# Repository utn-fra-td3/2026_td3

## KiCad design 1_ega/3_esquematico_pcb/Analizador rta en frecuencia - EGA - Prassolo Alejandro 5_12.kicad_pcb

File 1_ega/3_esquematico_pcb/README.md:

# esquemático y pcb

Subir en este directorio los archivos de esquemático y PCB en el software que se haya usado y sus vistas en .pdf.

## Esquema de conexiones actual (2026-11-14)

[Esquema modular editable, revision A](project_schematic.svg).
[Vista de impresion A3 horizontal](project_schematic.html).
Abrir la vista de impresion en un navegador y usar Imprimir / Guardar
como PDF. La exportacion automatica con Edge no produjo un archivo
verificable en esta sesion; no se incluye un PDF validado.
Los nombres de red iguales representan conexiones electricas. Los numeros
GPIO no son posiciones fisicas del conector.

Incluye ESP32-WROVER-E, AD9834, UART2, TFT KMRTM28028-SPI, MCP23017,
teclado 4x4 y filtros ADC propuestos. Los colores del cable MCP23017 y
los nombres de pads AD8302 provienen de las fotos recibidas. El dibujo
distingue la arquitectura existente de las conexiones propuestas: no es
un esquema conforme a obra ni un diseno listo para fabricar un PCB.

Siguen pendientes la alimentacion del breakout AD8302, el circuito de
alimentacion/backlight del TFT, el presupuesto de corriente y el frontend
RF. El usuario confirmo mejora del teclado HMI; detector y frontend RF
siguen sin validar. Para el AD8302 no
se debe interpretar la antigua referencia a 5 V de abajo como una
tension de alimentacion confirmada. El esquema deja VCC sin conectar.

## AD8302: frontend provisional (2026-11-07)

Objetivo vigente: DUT de 50 ohm, 100 kHz a 37.5 MHz, ganancia y fase plegada 0..180
grados. La foto del modulo no sustituye un esquema ni confirma ese rango.
No conectar siguiendo solamente el orden de pads de la foto rotada.

### Topologia inicial de prueba

```text
AD9834 Sine1 -> filtro/driver compatible con 50 ohm -> divisor resistivo
																										|          |
																						 DUT entrada     referencia
																										|          |
																						 DUT salida        |
																										|          |
																						 pad opcional  pad opcional
																										|          |
																							 INPA AD8302 INPB AD8302

VM (magnitud) -> aislamiento/filtro/proteccion -> GPIO36 ADC1_CH0
VP (fase)     -> aislamiento/filtro/proteccion -> GPIO34 ADC1_CH6
GND modulo    -> masa comun de senal/ESP32
VREF          -> sin conexion inicial; es una salida, no alimentacion
```

Esta topologia es condicional: INPA/INPB deben presentar las terminaciones
de 50 ohm previstas; si el modulo no las incorpora, redisenar o anadirlas
segun su esquema. INPA actua como carga de la salida del DUT. No anadir
otra carga de 50 ohm en paralelo sin incluirla en el presupuesto de carga.
La rama de referencia aproxima la tension de entrada del DUT solo con
ramas y cargas adaptadas; un DUT desadaptado exige muestreo en su plano
real de entrada o una correccion independiente de esa aproximacion.

Un divisor resistivo de tres puertos puede cubrir frecuencias bajas sin
transformador: tres resistencias nominales de 16.7 ohm en estrella dan
adaptacion de 50 ohm y aproximadamente 6 dB de perdida entre puertos,
cuando todos estan terminados en 50 ohm. Es una opcion de estudio, no un
PCB RF validado. Mantener cables de ramas equivalentes y layout compacto;
a decenas de MHz no usar protoboard ni largos cables Dupont para RF.
Un splitter comercial RF debe especificar funcionamiento a 100 kHz; muchos
no llegan a esa frecuencia. No conectar un tee de dos cargas de 50 ohm:
el generador veria 25 ohm.

La amplitud de 600 mVpp observada con osciloscopio de alta impedancia no
demuestra capacidad de excitar 50 ohm. Determinar impedancia y respuesta
cargada del modulo DDS antes de seleccionar buffer/filtro o atenuadores.
Si esos 600 mVpp fueran realmente sobre 50 ohm, serian unos -0.46 dBm.
El detector tiene rango operativo nominal de -60 a 0 dBm por entrada y
aproximadamente +/-30 dB de relacion. Mantener margen en ambos niveles y
en la relacion; comprobarlos con instrumentacion independiente.

### Conexion ADC y alimentacion

La asignacion GPIO34 es provisional; comprobar acceso fisico y ausencia
de otros usos. Dejar camara desconectada/deshabilitada: GPIO25/26 siguen
reservados para UART2. GPIO16/17 no estan disponibles por la PSRAM WROVER.

Como punto de partida de banco, estudiar resistencia serie de 1 kohm y
100 nF a masa junto a cada ADC: constante de tiempo de 100 us y corte de
aproximadamente 1.59 kHz. No son valores finales: verificar capacidad de
drive y estabilidad del modulo, carga del ADC y asentamiento combinado
con sus filtros. Anadir buffer/proteccion de baja fuga si lo exige el
presupuesto de error o la impedancia. No conectar RF bipolar a estos GPIO.

La marca de suministro parece indicar 5 V, pero verificar tension, polaridad,
regulador y desacoplo con vendedor/esquema antes de energizar. No alimentar
el modulo desde VREF ni desde VCC del adaptador UART. Las salidas del chip
son nominalmente de aproximadamente 0..1.8 V; comprobar las del modulo
antes de conectarlas al ESP32. No aplicar 5 V a GPIO del ESP32.

### Comprobaciones antes de cerrar esquema/BOM

- Obtener esquema o fotos nitidas de ambos lados y confirmar orden/funcion
	de pads, conexiones MSET/PSET y suministro del modulo.
- Verificar terminacion RF, capacitores de entrada, compensacion a baja
	frecuencia y filtros de salidas. Determinan si 100 kHz es alcanzable.
- Definir carga de fuente, divisor, DUT y detector, perdidas/atenuacion y
	amplitud cargada de ambas ramas en toda la banda.
- Revisar pureza del DDS y filtro cerca de 37.5 MHz; Nyquist no garantiza
	una senoide util para medicion.
- Seleccionar conectores/coax de 50 ohm, resistencias del divisor y pads
	solo despues de resolver impedancias. No hay BOM definitiva todavia.

### Secuencia de puesta en marcha

1. Cablear sin alimentacion; revisar masas, polaridad y cortocircuitos.
2. Verificar ADC con DC segura y DMM, sin modulo RF conectado.
3. Energizar modulo con fuente limitada en corriente y tension verificada;
	 comprobar VM/VP/VREF antes de conectarlos a los ADC.
4. Aplicar dos senales del mismo generador con carga y atenuacion conocidas;
	 empezar con margen, por ejemplo alrededor de -20 dBm en cada entrada.
5. Verificar thru y ganancia con atenuadores conocidos en ambas ramas;
	 comprobar signo, pendiente, offset y variacion con frecuencia.
6. Caracterizar fase con referencias verificadas, preferentemente puntos
	 interiores como 45/135 grados. Los extremos 0/180 son menos fiables.
7. Medir un DUT conocido y documentar error y rango realmente validado.

VM/VP no permiten verificar de forma fiable niveles absolutos ni ausencia
de senal. La fase plegada no distingue adelanto/atraso y una resta del thru
no recupera esa informacion. No se trata de un VNA completo ni mide S11.

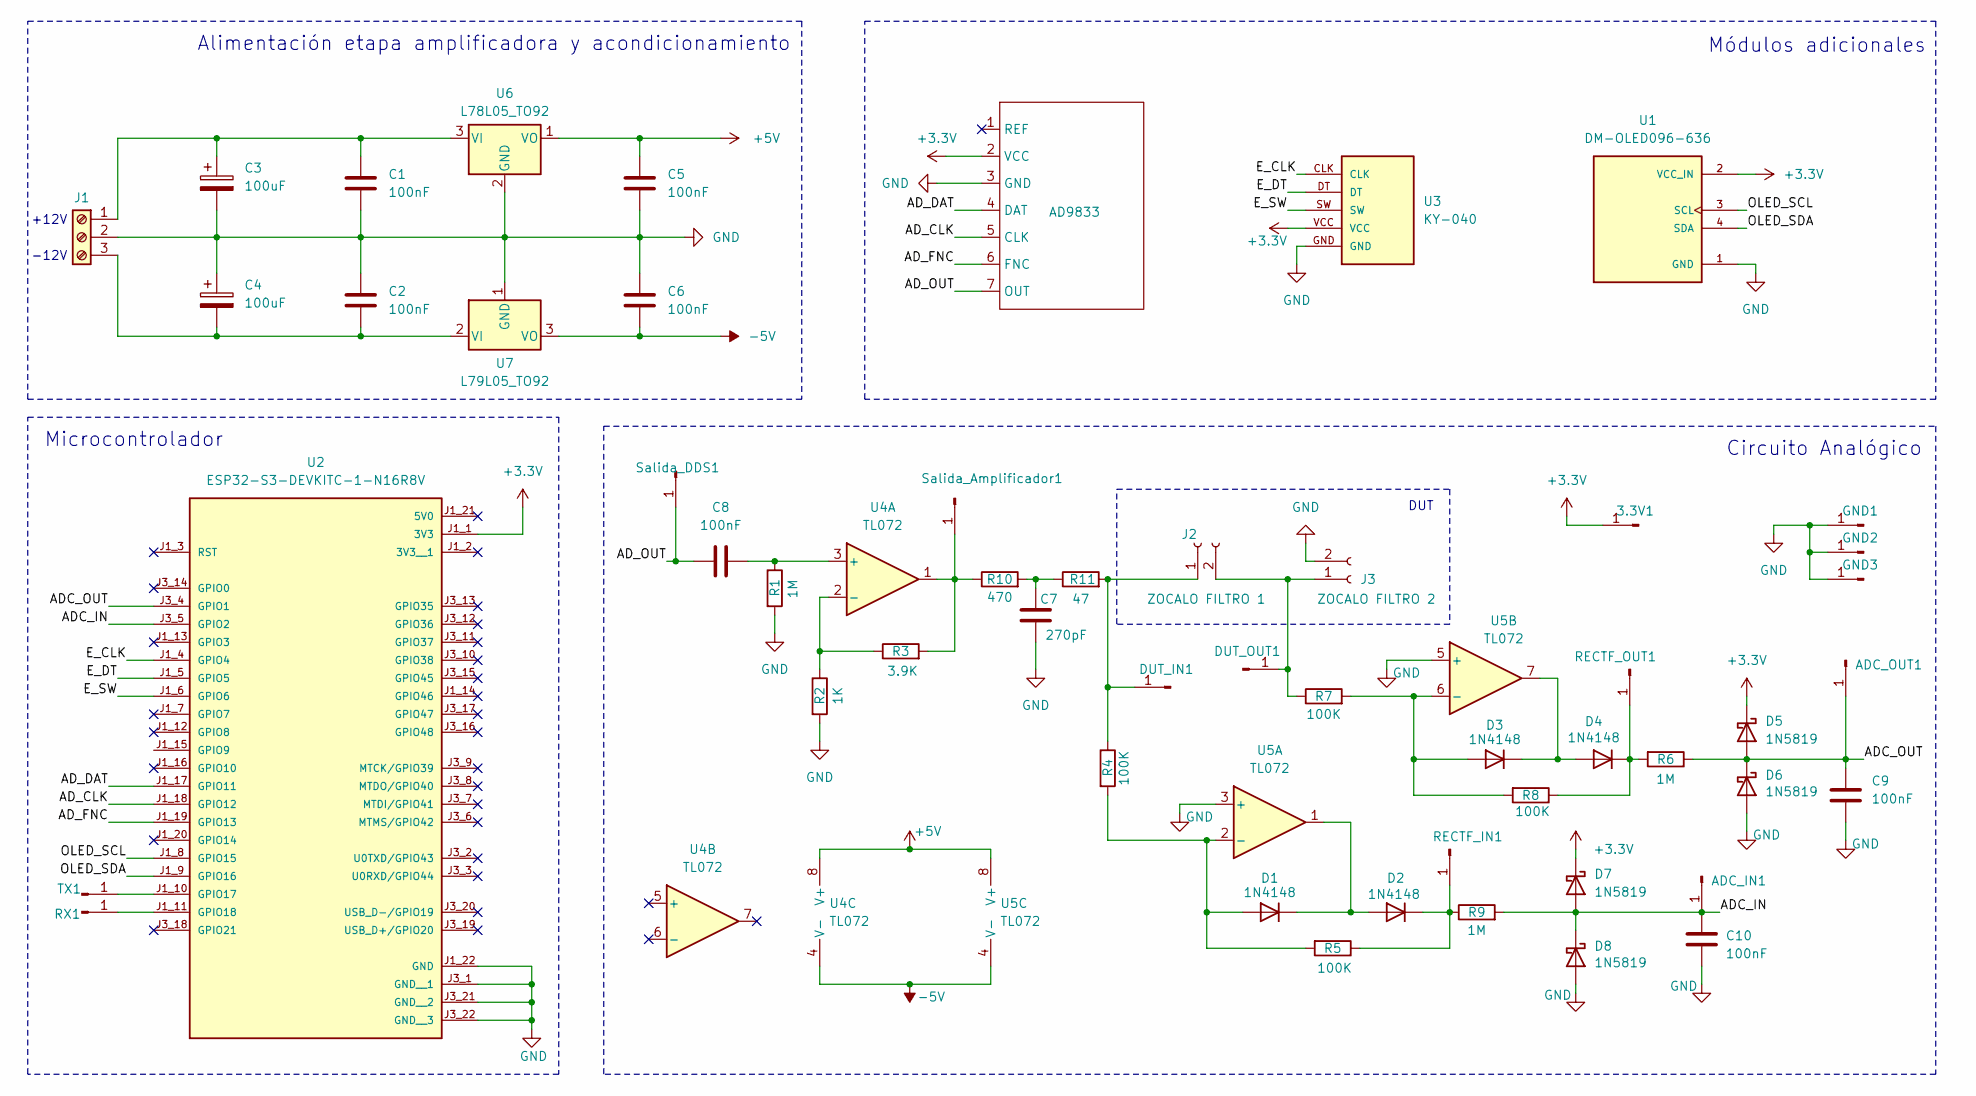
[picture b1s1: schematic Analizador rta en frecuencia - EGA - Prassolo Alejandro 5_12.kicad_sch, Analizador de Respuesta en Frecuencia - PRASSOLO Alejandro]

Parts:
3.3V1: Conn_01x01_Pin; PinHeader_1x01_P2.54mm_Vertical
AD9833: AD9833_MODULO
ADC_IN1: Conn_01x01_Pin; PinHeader_1x01_P2.54mm_Vertical
ADC_OUT1: Conn_01x01_Pin; PinHeader_1x01_P2.54mm_Vertical
C1, C2, C5, C6, C8, C9, C10: 100nF; C_Disc_D5.0mm_W2.5mm_P2.50mm
C3, C4: 100uF; CP_Radial_D6.3mm_P2.50mm
C7: 270pF; C_Disc_D5.0mm_W2.5mm_P2.50mm
D1, D2, D3, D4: 1N4148; D_DO-35_SOD27_P7.62mm_Horizontal
D5, D6, D7, D8: 1N5819; D_DO-41_SOD81_P10.16mm_Horizontal
DUT_IN1: Conn_01x01_Pin; PinHeader_1x01_P2.54mm_Vertical
DUT_OUT1: Conn_01x01_Pin; PinHeader_1x01_P2.54mm_Vertical
GND1, GND2, GND3: Conn_01x01_Pin; PinHeader_1x01_P2.54mm_Vertical
J1: Screw_Terminal_01x03; TerminalBlock_Phoenix_MKDS-1,5-3-5.08_1x03_P5.08mm_Horizont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
J2: ZOCALO FILTRO 1; PinSocket_1x02_P2.54mm_Vertical
J3: ZOCALO FILTRO 2; PinSocket_1x02_P2.54mm_Vertical
R1, R6, R9: 1M; R_Axial_DIN0207_L6.3mm_D2.5mm_P7.62mm_Horizontal
R2: 1K; R_Axial_DIN0207_L6.3mm_D2.5mm_P7.62mm_Horizontal
R3: 3.9K; R_Axial_DIN0207_L6.3mm_D2.5mm_P7.62mm_Horizontal
R4, R5, R7, R8: 100K; R_Axial_DIN0207_L6.3mm_D2.5mm_P7.62mm_Horizontal
R10: 470; R_Axial_DIN0207_L6.3mm_D2.5mm_P7.62mm_Horizontal
R11: 47; R_Axial_DIN0207_L6.3mm_D2.5mm_P7.62mm_Horizontal
RECTF_IN1: Conn_01x01_Pin; PinHeader_1x01_P2.54mm_Vertical
RECTF_OUT1: Conn_01x01_Pin; PinHeader_1x01_P2.54mm_Vertical
RX1: Conn_01x01_Pin; PinHeader_1x01_P2.54mm_Vertical
Salida_Amplificador1: Conn_01x01_Pin; PinHeader_1x01_P2.54mm_Vertical
Salida_DDS1: Conn_01x01_Pin; PinHeader_1x01_P2.54mm_Vertical
TX1: Conn_01x01_Pin; PinHeader_1x01_P2.54mm_Vertical
U1: DM-OLED096-636; MODULE_DM-OLED096-636; PARTREV 2018-09-10
U2: ESP32-S3-DEVKITC-1-N16R8V; XCVR_ESP32-S3-DEVKITC-1-N16R8V; PARTREV 1.1
U3: KY-040; KY-040-PORT
U4, U5: TL072; DIP-8_W7.62mm_Socket
U6: L78L05_TO92; TO-92_Inline
U7: L79L05_TO92; TO-92_Inline

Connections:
+3.3V: 3.3V1.1 (Pin_1_1), AD9833.2 (VCC), D5.1 (K), D7.1 (K), U1.2 (VCC_IN), U2.J1_1 (3V3), U3.VCC
+5V: C5.1, U4.8 (V+), U5.8 (V+), U6.1 (VO)
-5V: C6.2, U4.4 (V-), U5.4 (V-), U7.3 (VO)
/ADC_IN: ADC_IN1.1 (Pin_1_1), C10.1, D7.2 (A), D8.1 (K), R9.2, U2.J3_5 (GPIO2)
/ADC_OUT: ADC_OUT1.1 (Pin_1_1), C9.1, D5.2 (A), D6.1 (K), R6.1, U2.J3_4 (GPIO1)
/AD_CLK: AD9833.5 (CLK), U2.J1_18 (GPIO12)
/AD_DAT: AD9833.4 (DAT), U2.J1_17 (GPIO11)
/AD_FNC: AD9833.6 (FNC), U2.J1_19 (GPIO13)
/AD_OUT: AD9833.7 (OUT), C8.1, Salida_DDS1.1 (Pin_1_1)
/E_CLK: U2.J1_4 (GPIO4), U3.CLK
/E_DT: U2.J1_5 (GPIO5), U3.DT
/E_SW: U2.J1_6 (GPIO6), U3.SW
/OLED_SCL: U1.3 (SCL), U2.J1_8 (GPIO15)
/OLED_SDA: U1.4 (SDA), U2.J1_9 (GPIO16)
GND: AD9833.3 (GND), C1.2, C2.1, C3.2, C4.1, C5.2, C6.1, C7.2, C9.2, C10.2, D6.2 (A), D8.2 (A), GND1.1 (Pin_1_1), GND2.1 (Pin_1_1), GND3.1 (Pin_1_1), J1.2, J3.2, R1.2, R2.2, U1.1 (GND), U2.J1_22 (GND), U2.J3_1 (GND__1), U2.J3_21 (GND__2), U2.J3_22 (GND__3), U3.GND, U5.3 (+), U5.5 (+), U6.2 (GND), U7.1 (GND)
unnamed: C7.1, R10.2, R11.1
unnamed: D1.2 (A), R4.2, R5.2, U5.2 (-)
unnamed: D1.1 (K), D2.2 (A), U5.1
unnamed: D2.1 (K), R5.1, R9.1, RECTF_IN1.1 (Pin_1_1)
unnamed: D3.2 (A), R7.2, R8.2, U5.6 (-)
unnamed: D3.1 (K), D4.2 (A), U5.7
unnamed: D4.1 (K), R6.2, R8.1, RECTF_OUT1.1 (Pin_1_1)
unnamed: DUT_IN1.1 (Pin_1_1), J2.1, R4.1, R11.2
unnamed: DUT_OUT1.1 (Pin_1_1), J2.2, J3.1, R7.1
unnamed: C1.1, C3.1, J1.1, U6.3 (VI)
unnamed: C2.2, C4.2, J1.3, U7.2 (VI)
unnamed: RX1.1 (Pin_1_1), U2.J1_11 (GPIO18)
unnamed: R3.2, R10.1, Salida_Amplificador1.1 (Pin_1_1), U4.1
unnamed: TX1.1 (Pin_1_1), U2.J1_10 (GPIO17)
unnamed: C8.2, R1.1, U4.3 (+)
unnamed: R2.1, R3.1, U4.2 (-)

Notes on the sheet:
Circuito Analógico
DUT
Microcontrolador
Alimentación etapa amplificadora y acondicionamiento
-12V
+12V
Módulos adicionales

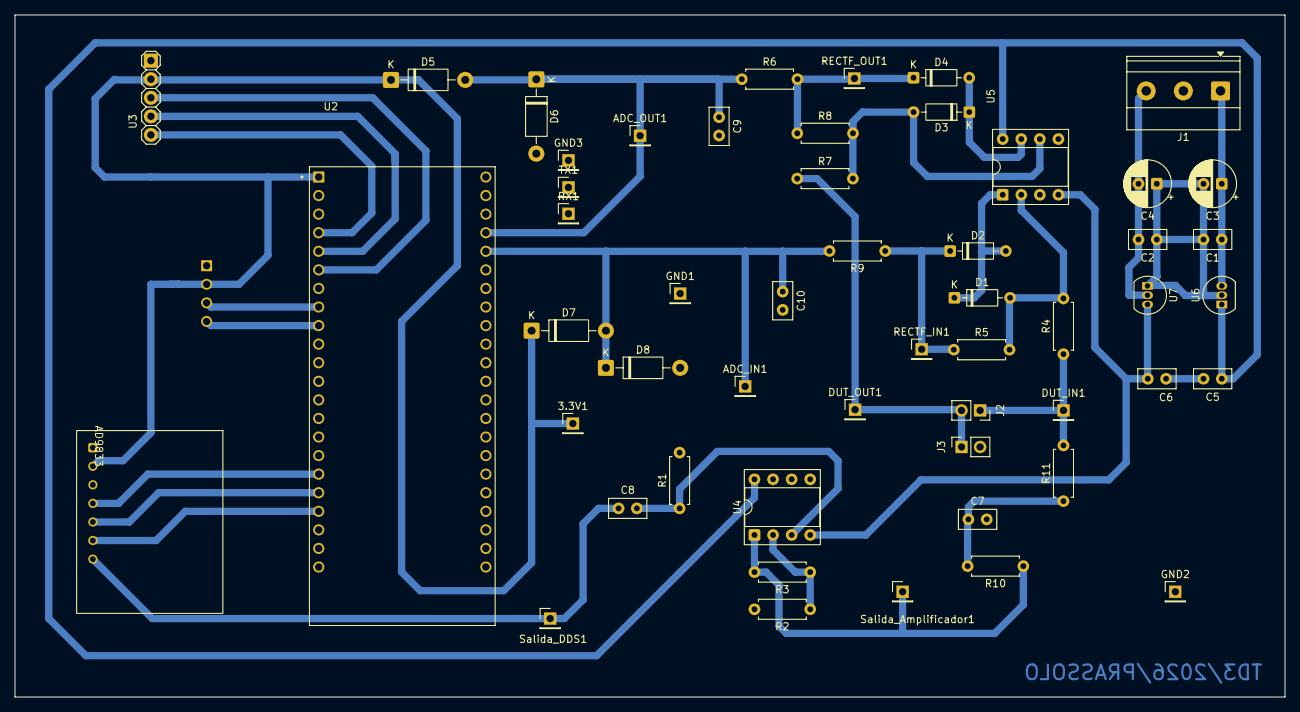
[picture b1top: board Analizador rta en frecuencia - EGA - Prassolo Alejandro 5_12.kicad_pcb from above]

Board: 2 copper layers, 173.7 x 93.3 mm, 54 parts (0 on the bottom side), 31 nets.

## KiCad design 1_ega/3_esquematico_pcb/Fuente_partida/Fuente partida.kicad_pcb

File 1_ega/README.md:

# Proyecto

## EGA: analizador de respuesta en frecuencia

ESP32-WROVER-E, DDS AD9834 y detector AD8302 para ganancia y fase plegada.
Rango admitido por software: **100 kHz a 37.5 MHz**, inclusive, con MCLK
configurado en 75 MHz. No equivale a una banda de medicion RF calibrada.

- [Firmware, GUI/CLI y pruebas](2_workspace/firmware/README.md).
- [Comandos PowerShell de compilacion y carga](2_workspace/firmware/Terminal_command_cheatcode.yaml),
  con Python ESP-IDF explicito y bloques separados `hmi_build`/`hmi_flash`.
- [Esquema y frontend provisional](3_esquematico_pcb/README.md).
- [Diagramas de tareas y bloques](5_referencias/README.md).

La HMI local permite configurar un barrido SINE y ver ganancia/fase en vivo;
A cancela el barrido local y vuelve al inicio. TFT y teclado estan conectados;
el usuario confirmo mejora del teclado con escaneo independiente. AD8302
permanece desconectado: usar SIM hasta validar el frontend.

## Templates para informe IEEE

* [LaTeX en Overleaf](https://www.overleaf.com/latex/templates/ieee-conference-template/grfzhhncsfqn)
* [Google Docs](https://docs.google.com/document/d/1DDDHbyujVE0Jso3ITDVRpF-n_ydSYhf2IecZ8xTA-0w/preview?markAsViewed=false&tab=t.0)

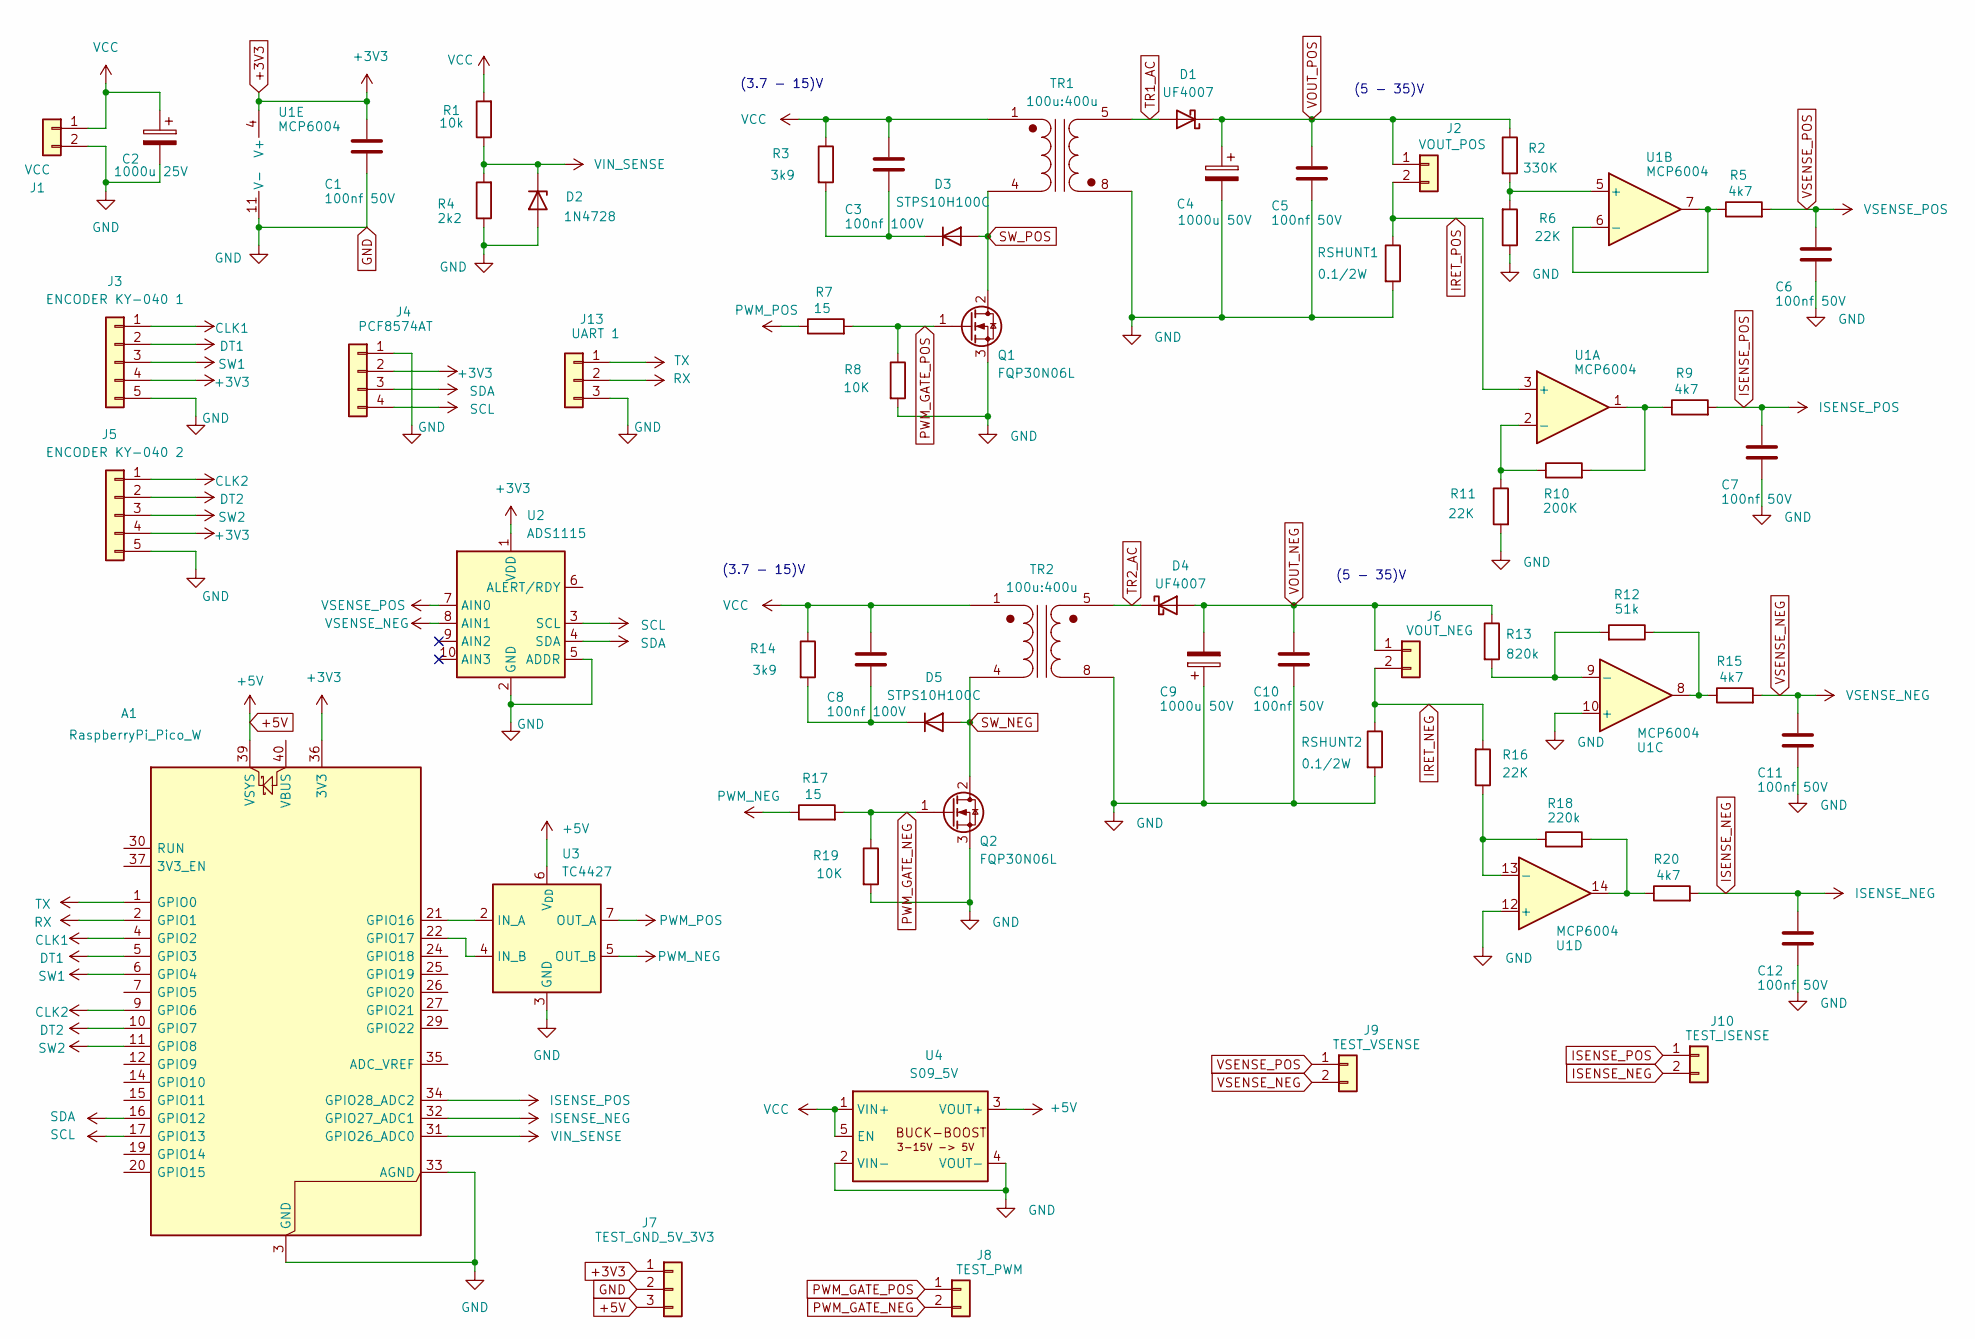
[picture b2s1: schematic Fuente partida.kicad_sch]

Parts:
A1: RaspberryPi_Pico_W; RaspberryPi_Pico_W_Pads_Anchos_Sin_Keepout_Antena
C1, C5, C6, C7, C10, C11, C12: 100nf 50V; C_Disc_D5.0mm_W2.5mm_P5.00mm
C2: 1000u 25V; CP_Radial_D10.0mm_P5.00mm
C3, C8: 100nf 100V; C_Disc_D5.0mm_W2.5mm_P5.00mm
C4, C9: 1000u 50V; CP_Radial_D16.0mm_P7.50mm
D1, D4: UF4007; D_DO-15_P10.16mm_Horizontal
D2: 1N4728; D_DO-41_SOD81_P10.16mm_Horizontal
D3, D5: STPS10H100C; D_DO-41_SOD81_P10.16mm_Horizontal
J1: VCC; TerminalBlock_MaiXu_MX126-5.0-02P_1x02_P5.00mm
J2: VOUT_POS; TerminalBlock_MaiXu_MX126-5.0-02P_1x02_P5.00mm
J3: ENCODER KY-040 1; PinSocket_1x05_P2.54mm_Vertical
J4: PCF8574AT; PinSocket_1x04_P2.54mm_Vertical
J5: ENCODER KY-040 2; PinSocket_1x05_P2.54mm_Vertical
J6: VOUT_NEG; TerminalBlock_MaiXu_MX126-5.0-02P_1x02_P5.00mm
J7: TEST_GND_5V_3V3; JST_XH_B3B-XH-A_1x03_P2.50mm_Vertical
J8: TEST_PWM; JST_XH_B2B-XH-A_1x02_P2.50mm_Vertical
J9: TEST_VSENSE; JST_XH_B2B-XH-A_1x02_P2.50mm_Vertical
J10: TEST_ISENSE; JST_XH_B2B-XH-A_1x02_P2.50mm_Vertical
J13: UART 1; PinSocket_1x03_P2.54mm_Vertical
Q1, Q2: FQP30N06L; TO-220-3_Vertical_P3.81mm
R1: 10k; R_Axial_DIN0204_L3.6mm_D1.6mm_P7.62mm_Horizontal
R2: 330K; R_Axial_DIN0204_L3.6mm_D1.6mm_P7.62mm_Horizontal
R3, R14: 3k9; R_Axial_DIN0204_L3.6mm_D1.6mm_P7.62mm_Horizontal
R4: 2k2; R_Axial_DIN0204_L3.6mm_D1.6mm_P7.62mm_Horizontal
R5, R9, R15, R20: 4k7; R_Axial_DIN0204_L3.6mm_D1.6mm_P7.62mm_Horizontal
R6, R11, R16: 22K; R_Axial_DIN0204_L3.6mm_D1.6mm_P7.62mm_Horizontal
R7, R17: 15; R_Axial_DIN0204_L3.6mm_D1.6mm_P7.62mm_Horizontal
R8, R19: 10K; R_Axial_DIN0204_L3.6mm_D1.6mm_P7.62mm_Horizontal
R10: 200K; R_Axial_DIN0204_L3.6mm_D1.6mm_P7.62mm_Horizontal
R12: 51k; R_Axial_DIN0204_L3.6mm_D1.6mm_P7.62mm_Horizontal
R13: 820k; R_Axial_DIN0204_L3.6mm_D1.6mm_P7.62mm_Horizontal
R18: 220k; R_Axial_DIN0204_L3.6mm_D1.6mm_P7.62mm_Horizontal
RSHUNT1, RSHUNT2: 0.1/2W; R_Axial_DIN0516_L15.5mm_D5.0mm_P7.62mm_Vertical
TR1, TR2: 100u:400u; Bobina_4P_30.5mm_P1_P4_P5_P8
U1: MCP6004; DIP-14_W7.62mm
U2: ADS1115; ADS1115_Modulo_1x10_Pads_Corregidos
U3: TC4427; DIP-8_W7.62mm
U4: S09_5V; S09_5V_BuckBoost_19x14mm

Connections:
+3V3: A1.36 (3V3), C1.1, J3.4, J4.2, J5.4, J7.1, U1.4 (V+), U2.1 (VDD)
+5V: A1.39 (VSYS), J7.3, U3.6 (V_{DD}), U4.3 (VOUT+)
CLK1: A1.4 (GPIO2), J3.1
CLK2: A1.9 (GPIO6), J5.1
DT1: A1.5 (GPIO3), J3.2
DT2: A1.10 (GPIO7), J5.2
GND: A1.3 (GND), A1.8 (GND), A1.13 (GND), A1.18 (GND), A1.23 (GND), A1.28 (GND), A1.33 (AGND), A1.38 (GND), C1.2, C2.2, C4.2, C5.2, C6.2, C7.2, C9.1, C10.2, C11.2, C12.2, D2.2 (A), J1.2, J3.5, J4.1, J5.5, J7.2, J13.3, Q1.3 (S), Q2.3 (S), R4.1, R6.1, R8.2, R11.2, R19.2, RSHUNT1.2, RSHUNT2.2, TR1.8 (SA), TR2.8 (SA), U1.10 (+), U1.11 (V-), U1.12 (+), U2.2 (GND), U2.5 (ADDR), U3.3 (GND), U4.2 (VIN-), U4.4 (VOUT-)
IRET_NEG: J6.2, R16.2, RSHUNT2.1
IRET_POS: J2.2, RSHUNT1.1, U1.3 (+)
ISENSE_NEG: A1.32 (GPIO27_ADC1), C12.1, J10.2, R20.2
ISENSE_POS: A1.34 (GPIO28_ADC2), C7.1, J10.1, R9.2
unnamed: A1.21 (GPIO16), U3.2 (IN_A)
unnamed: A1.22 (GPIO17), U3.4 (IN_B)
unnamed: C3.2, D3.1 (K), R3.2
unnamed: C8.2, D5.1 (K), R14.2
unnamed: R9.1, R10.2, U1.1
unnamed: R12.1, R15.1, U1.8
unnamed: R18.2, R20.1, U1.14
unnamed: R10.1, R11.1, U1.2 (-)
unnamed: R2.2, R6.2, U1.5 (+)
unnamed: R5.1, U1.6 (-), U1.7
unnamed: R12.2, R13.2, U1.9 (-)
unnamed: R16.1, R18.1, U1.13 (-)
PWM_GATE_NEG: J8.2, Q2.1 (G), R17.2, R19.1
PWM_GATE_POS: J8.1, Q1.1 (G), R7.2, R8.1
PWM_NEG: R17.1, U3.5 (OUT_B)
PWM_POS: R7.1, U3.7 (OUT_A)
RX: A1.2 (GPIO1), J13.2
SCL: A1.17 (GPIO13), J4.4, U2.3 (SCL)
SDA: A1.16 (GPIO12), J4.3, U2.4 (SDA)
SW1: A1.6 (GPIO4), J3.3
SW2: A1.11 (GPIO8), J5.3
SW_NEG: D5.2 (A), Q2.2 (D), TR2.4 (AB)
SW_POS: D3.2 (A), Q1.2 (D), TR1.4 (AB)
TR1_AC: D1.2 (A), TR1.5 (SB)
TR2_AC: D4.1 (K), TR2.5 (SB)
TX: A1.1 (GPIO0), J13.1
VCC: C2.1, C3.1, C8.1, J1.1, R1.2, R3.1, R14.1, TR1.1 (AA), TR2.1 (AA), U4.1 (VIN+), U4.5 (EN)
VIN_SENSE: A1.31 (GPIO26_ADC0), D2.1 (K), R1.1, R4.2
VOUT_NEG: C9.2, C10.1, D4.2 (A), J6.1, R13.1
VOUT_POS: C4.1, C5.1, D1.1 (K), J2.1, R2.1
VSENSE_NEG: C11.1, J9.2, R15.2, U2.8 (AIN1)
VSENSE_POS: C6.1, J9.1, R5.2, U2.7 (AIN0)

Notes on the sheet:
(5 - 35)V
(3.7 - 15)V

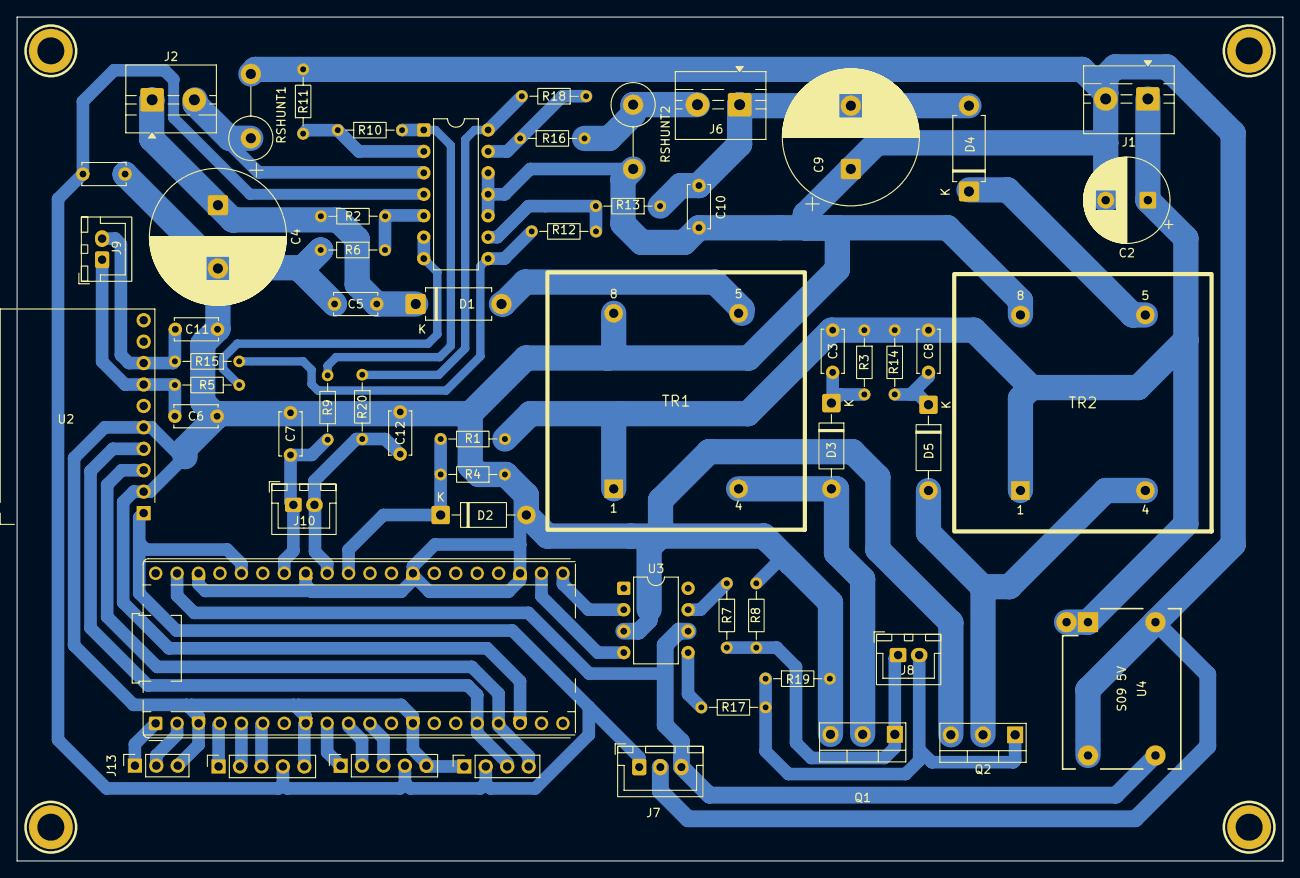
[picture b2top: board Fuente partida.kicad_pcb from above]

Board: 2 copper layers, 150.0 x 100.0 mm, 63 parts (0 on the bottom side), 43 nets.

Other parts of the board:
H1, H2, H3, H4: M3; MountingHole_3.2mm_M3_Pad_CNC

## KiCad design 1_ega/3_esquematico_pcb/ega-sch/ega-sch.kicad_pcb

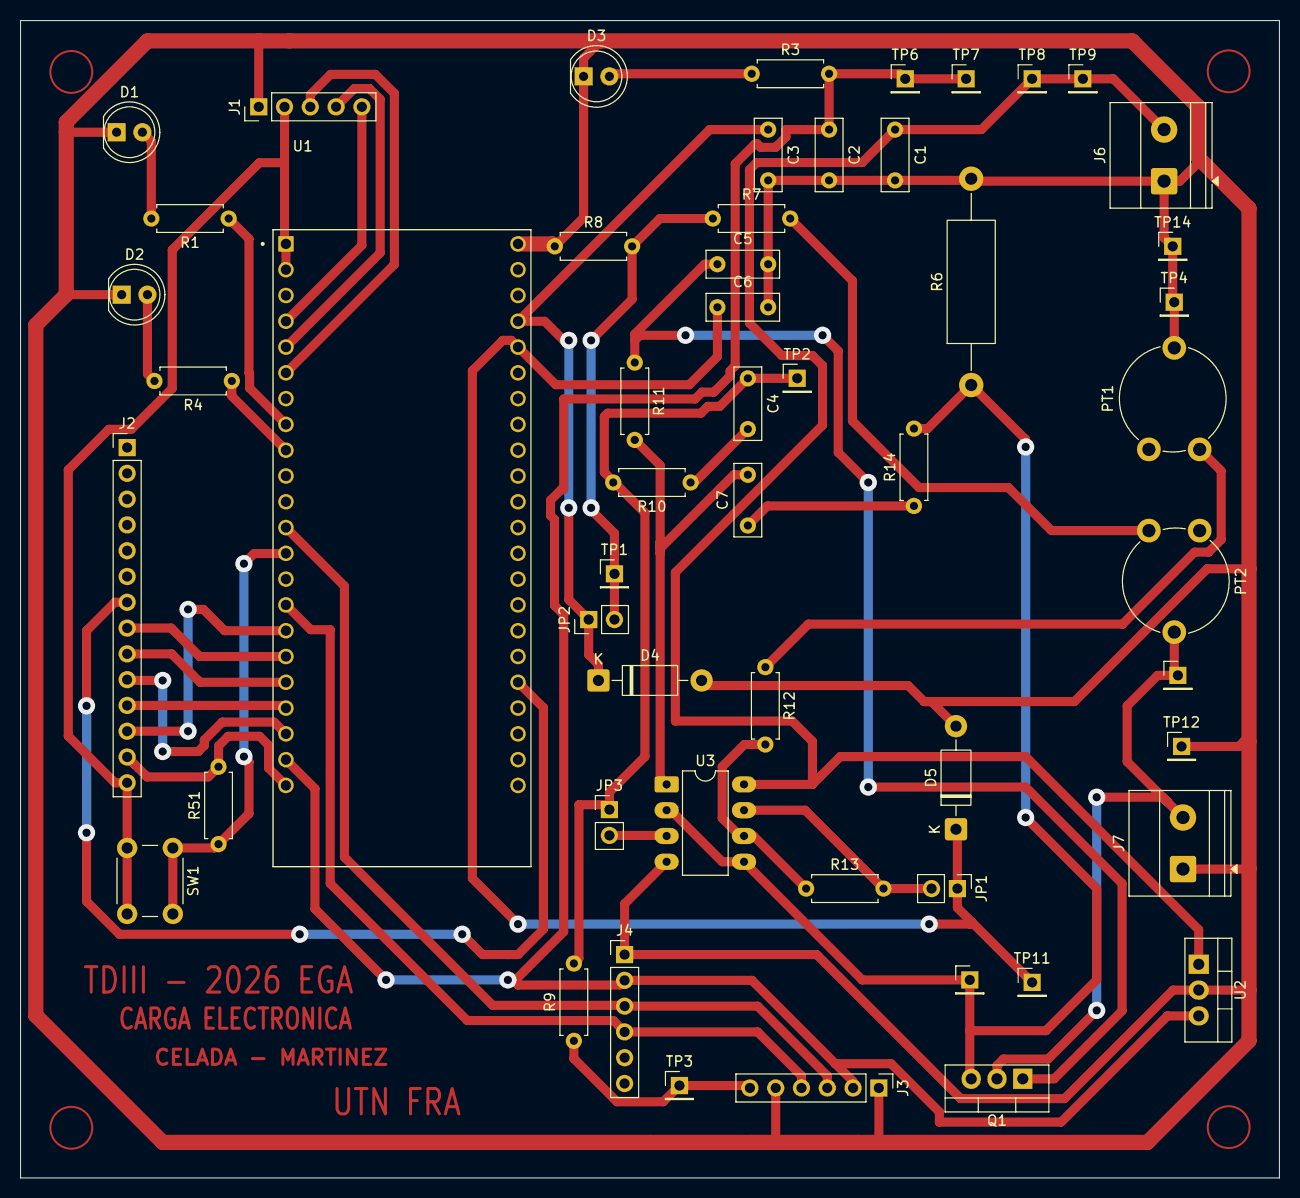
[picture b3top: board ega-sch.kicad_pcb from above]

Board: 2 copper layers, 124.0 x 114.0 mm, 54 parts (0 on the bottom side), 37 nets.

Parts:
C1, C2: 0,33uF; C_Disc_D7.0mm_W2.5mm_P5.00mm
C3, C4, C6: 100nF; C_Disc_D7.0mm_W2.5mm_P5.00mm
C5: 10nF; C_Disc_D7.0mm_W2.5mm_P5.00mm
C7: 1nF; C_Disc_D7.0mm_W2.5mm_P5.00mm
D1, D2: LD271; LED_D5.0mm_IRGrey
D3: ENCENDIDO; LED_D5.0mm_FlatTop
D4, D5: 1N4728A; D_DO-41_SOD81_P10.16mm_Horizontal
J1: Encoder; PinHeader_1x05_P2.54mm_Vertical
J2: TFT_Display; PinHeader_1x14_P2.54mm_Vertical
J3: MCP4725; PinHeader_1x06_P2.54mm_Vertical
J4: DS3231; PinHeader_1x06_P2.54mm_Vertical
J6: V+; TerminalBlock_Phoenix_MKDS-1,5-2-5.08_1x02_P5.08mm_Horizont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
J7: Ventrada; TerminalBlock_Phoenix_MKDS-1,5-2-5.08_1x02_P5.08mm_Horizont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
JP1, JP2, JP3: Jumper; PinHeader_1x02_P2.54mm_Vertical
PT1, PT2: PRESET 1K; Potentiometer_Piher_PT-10-V10_Vertical
Q1: IRFZ44; TO-220-3_Vertical
R1, R4: 330; R_Axial_DIN0207_L6.3mm_D2.5mm_P7.62mm_Horizontal
R3: 1K; R_Axial_DIN0207_L6.3mm_D2.5mm_P7.62mm_Horizontal
R6: Rshunt; R_Axial_DIN0414_L11.9mm_D4.5mm_P20.32mm_Horizontal
R7: 12K; R_Axial_DIN0207_L6.3mm_D2.5mm_P7.62mm_Horizontal
R8: 4,7K; R_Axial_DIN0207_L6.3mm_D2.5mm_P7.62mm_Horizontal
R9, R10, R12, R14, R51: 10K; R_Axial_DIN0207_L6.3mm_D2.5mm_P7.62mm_Horizontal
R11: 100; R_Axial_DIN0207_L6.3mm_D2.5mm_P7.62mm_Horizontal
R13: 3,3K; R_Axial_DIN0207_L6.3mm_D2.5mm_P7.62mm_Horizontal
SW1: SW_Push; SW_PUSH_6mm_H5mm
TP1: ADC_VIN; PinHeader_1x01_P2.54mm_Vertical
TP2: DAC; PinHeader_1x01_P2.54mm_Vertical
TP3: VDAC; PinHeader_1x01_P2.54mm_Vertical
TP4, TP14: GND; PinHeader_1x01_P2.54mm_Vertical
TP5: VIN; PinHeader_1x01_P2.54mm_Vertical
TP6, TP7: +5V; PinHeader_1x01_P2.54mm_Vertical
TP8, TP9: +12V; PinHeader_1x01_P2.54mm_Vertical
TP10: VSENS; PinHeader_1x01_P2.54mm_Vertical
TP11: ADC_VSENS; PinHeader_1x01_P2.54mm_Vertical
TP12: GND2; PinHeader_1x01_P2.54mm_Vertical
U1: ESP32-S3-DEVKITC-1-N16R8V; XCVR_ESP32-S3-DEVKITC-1-N16R8V
U2: LM7805_TO220; TO-220-3_Vertical
U3: LM358; DIP-8_W7.62mm_LongPads

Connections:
+3V3: J1.2, J2.14, SW1.2, U1.J1_1 (3V3), U1.J1_2 (3V3)
+5V: C2.1, J3.2, J4.2, R3.2, TP6.1, TP7.1, U1.J1_21 (5V0), U2.3 (VO)
+12V: C1.1, J6.2, TP8.1, TP9.1, U2.1 (VI), U3.8 (V+)
/Vin: J7.2, PT2.2, Q1.2 (D), TP5.1
ADC_VIN: C3.1, D4.1 (K), JP2.1 (A), U1.J3_4 (GPIO1)
ADC_VSENS: C6.1, D5.1 (K), JP1.1 (A), TP11.1, U1.J3_5 (GPIO2)
CLK: J1.5, U1.J1_4 (GPIO4)
DAC: J3.6, R9.1, TP3.1
DT: J1.4, U1.J1_5 (GPIO5)
GND: C1.2, C2.2, C3.2, C5.2, C6.2, D1.1 (K), D2.1 (K), D3.1 (K), D4.2 (A), D5.2 (A), J1.1, J2.13, J3.1, J3.5, J4.1, J6.1, J7.1, PT1.2, R6.2, R8.1, R51.2, TP4.1, TP12.1, TP14.1, U1.J1_22 (GND), U1.J3_1 (GND), U1.J3_21 (GND), U1.J3_22 (GND), U2.2 (GND), U3.4 (V-)
GND2: C4.2, R10.1
I2C0_SCL: J3.4, J4.4, U1.J1_15 (GPIO9)
I2C0_SDA: J3.3, J4.3, U1.J1_12 (GPIO8)
LED_MAX: R4.1, U1.J1_9 (GPIO16)
LED_MIN: R1.1, U1.J1_8 (GPIO15)
unnamed: C7.1, R14.1
unnamed: C7.2, R11.2, U3.1
unnamed: D1.2 (A), R1.2
unnamed: D2.2 (A), R4.2
unnamed: D3.2 (A), R3.1
unnamed: JP1.2 (B), R13.2, U3.7
unnamed: JP2.2 (B), R7.1, R8.2, TP1.1
unnamed: C4.1, JP3.1 (A), R9.2, R10.2, TP2.1
unnamed: JP3.2 (B), U3.3 (+)
unnamed: PT1.1, R12.1
unnamed: PT2.1, R7.2
unnamed: C5.1, Q1.1 (G), R11.1
unnamed: Q1.3 (S), R6.1, R14.2, TP10.1, U3.2 (-), U3.5 (+)
unnamed: R12.2, R13.1, U3.6 (-)
SW: J1.3, U1.J1_6 (GPIO6)
SW_CONFIG: R51.1, SW1.1, U1.J1_13 (GPIO3)
TFT_CS: J2.12, U1.J1_16 (GPIO10)
TFT_DC: J2.10, U1.J1_20 (GPIO14)
TFT_LED: J2.7, U1.J3_18 (GPIO21)
TFT_RESET: J2.11, U1.J1_19 (GPIO13)
TFT_SCK: J2.8, U1.J1_17 (GPIO11)
TFT_SDI: J2.9, U1.J1_18 (GPIO12)

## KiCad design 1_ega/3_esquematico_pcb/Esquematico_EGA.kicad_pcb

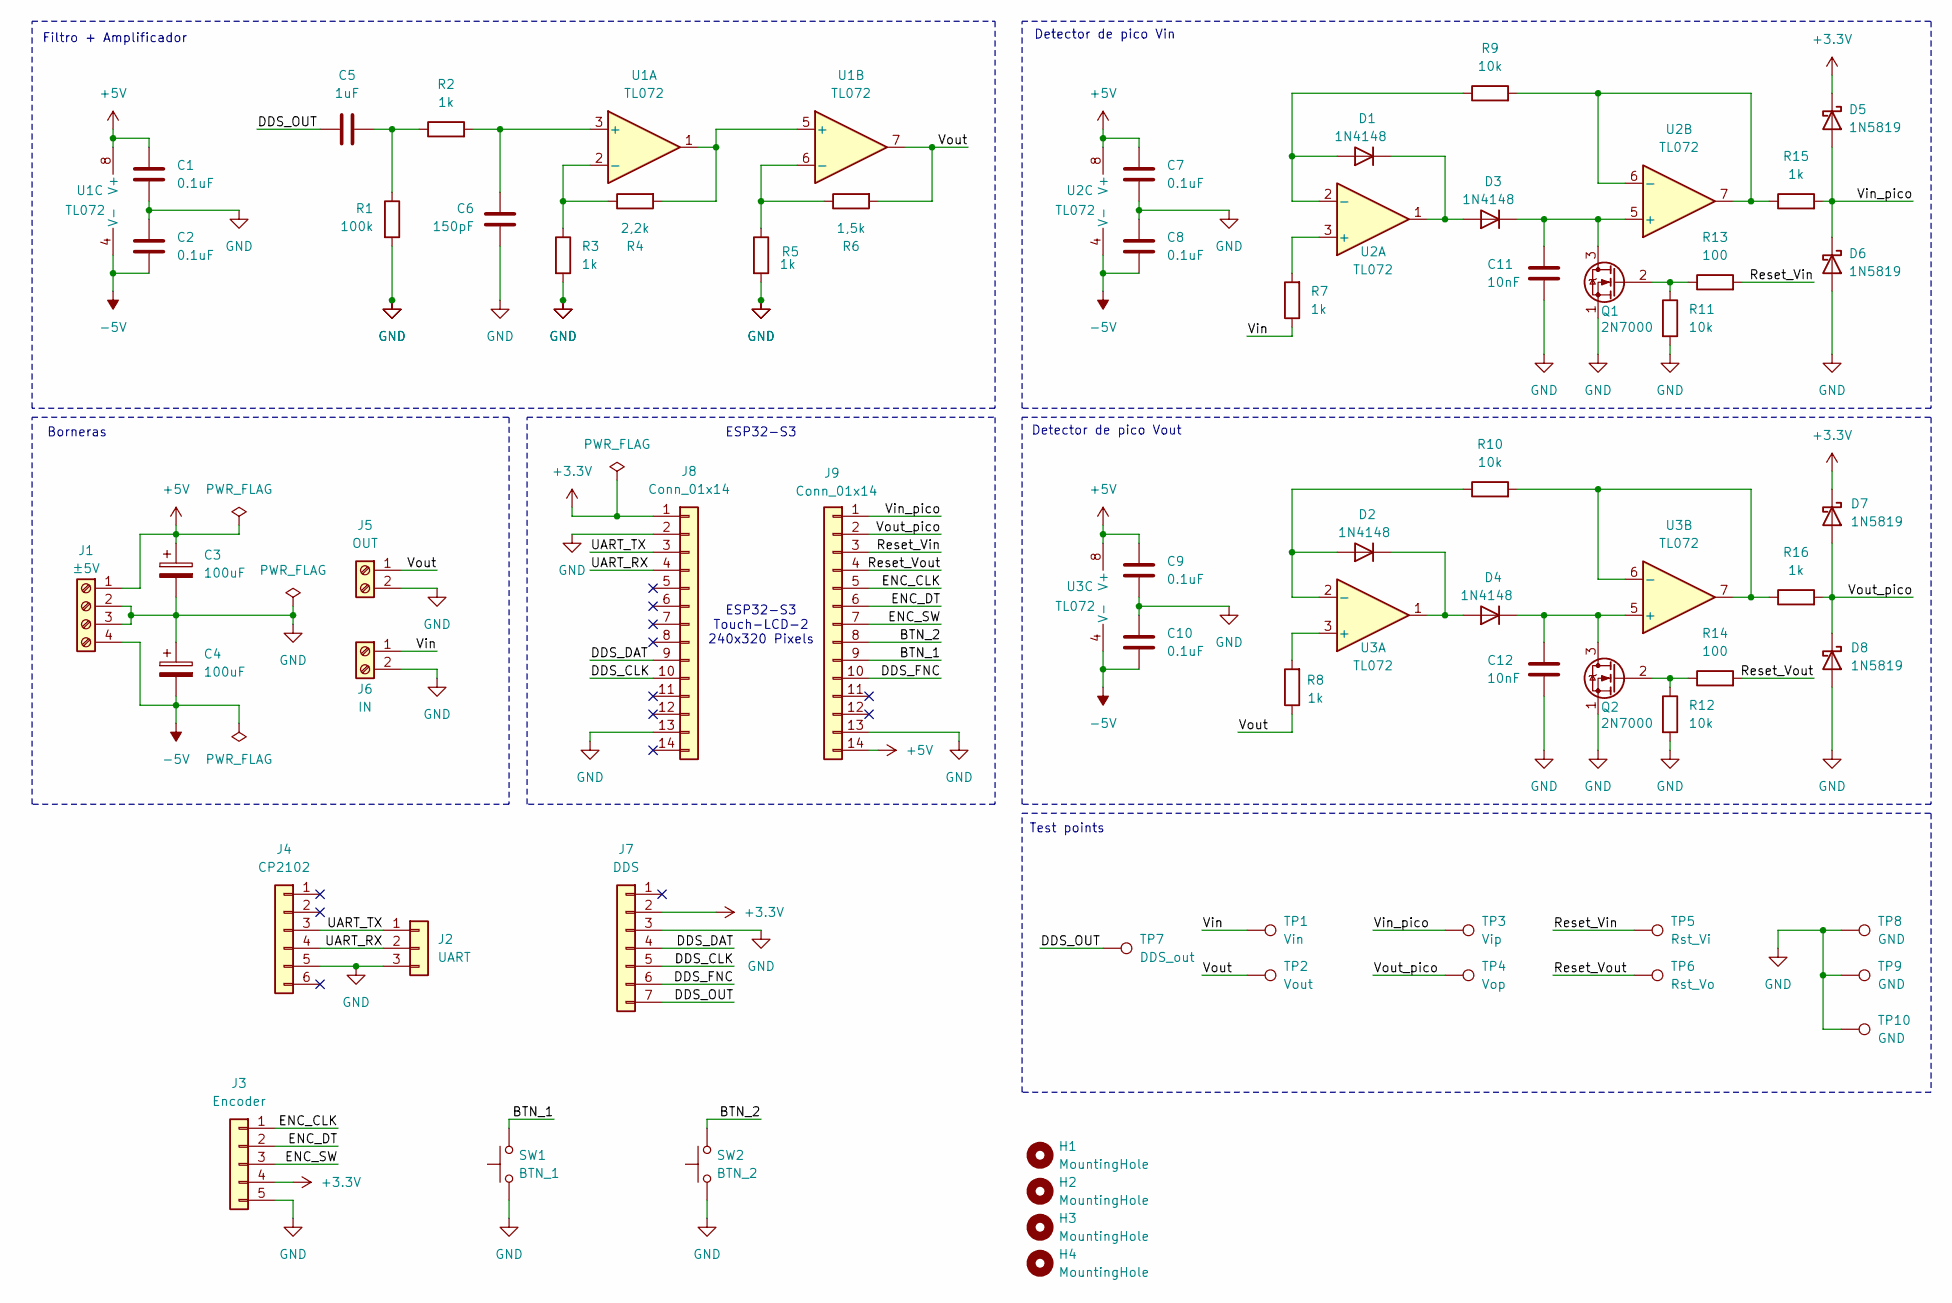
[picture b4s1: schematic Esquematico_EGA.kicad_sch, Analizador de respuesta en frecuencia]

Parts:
C1, C2, C7, C8, C9, C10: 0.1uF; C_Disc_D5.0mm_W2.5mm_P2.50mm
C3, C4: 100uF; CP_Radial_D7.5mm_P2.50mm
C5: 1uF; C_Disc_D5.0mm_W2.5mm_P5.00mm
C6: 150pF; C_Disc_D5.0mm_W2.5mm_P2.50mm
C11, C12: 10nF; C_Disc_D5.0mm_W2.5mm_P5.00mm
D1, D2, D3, D4: 1N4148; D_DO-35_SOD27_P7.62mm_Horizontal
D5, D6, D7, D8: 1N5819; D_DO-41_SOD81_P10.16mm_Horizontal
H1, H2, H3, H4: MountingHole; MountingHole_3.2mm_M3
J1: ±5V; TerminalBlock_Phoenix_MKDS-1,5-4-5.08_1x04_P5.08mm_Horizont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
J2: UART; PinSocket_1x03_P2.54mm_Vertical
J3: Encoder; PinSocket_1x05_P2.54mm_Vertical
J4: CP2102; PinSocket_1x06_P2.54mm_Vertical
J5: OUT; TerminalBlock_Phoenix_MKDS-1,5-2-5.08_1x02_P5.08mm_Horizont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
J6: IN; TerminalBlock_Phoenix_MKDS-1,5-2-5.08_1x02_P5.08mm_Horizont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
J7: DDS; PinSocket_1x07_P2.54mm_Vertical
J8, J9: Conn_01x14; PinSocket_1x14_P2.54mm_Vertical
Q1, Q2: 2N7000; TO-92_Inline_Wide
R1: 100k; R_Axial_DIN0207_L6.3mm_D2.5mm_P10.16mm_Horizontal
R2, R3, R5, R7, R8, R15, R16: 1k; R_Axial_DIN0207_L6.3mm_D2.5mm_P10.16mm_Horizontal
R4: 2,2k; R_Axial_DIN0207_L6.3mm_D2.5mm_P10.16mm_Horizontal
R6: 1,5k; R_Axial_DIN0207_L6.3mm_D2.5mm_P10.16mm_Horizontal
R9, R10, R11, R12: 10k; R_Axial_DIN0207_L6.3mm_D2.5mm_P10.16mm_Horizontal
R13, R14: 100; R_Axial_DIN0207_L6.3mm_D2.5mm_P10.16mm_Horizontal
SW1: BTN_1; SW_PUSH_6mm_H5mm
SW2: BTN_2; SW_PUSH_6mm_H5mm
TP1: Vin; PinHeader_1x01_P2.54mm_Vertical
TP2: Vout; PinHeader_1x01_P2.54mm_Vertical
TP3: Vip; PinHeader_1x01_P2.54mm_Vertical
TP4: Vop; PinHeader_1x01_P2.54mm_Vertical
TP5: Rst_Vi; PinHeader_1x01_P2.54mm_Vertical
TP6: Rst_Vo; PinHeader_1x01_P2.54mm_Vertical
TP7: DDS_out; PinHeader_1x01_P2.54mm_Vertical
TP8, TP9, TP10: GND; PinHeader_1x01_P2.54mm_Vertical
U1, U2, U3: TL072; DIP-8_W7.62mm_LongPads

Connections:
+3.3V: D5.1 (K), D7.1 (K), J3.4, J7.2, J8.1
+5V: C1.1, C3.1, C7.1, C9.1, J1.1, J9.14, U1.8 (V+), U2.8 (V+), U3.8 (V+)
-5V: C2.2, C4.2, C8.2, C10.2, J1.4, U1.4 (V-), U2.4 (V-), U3.4 (V-)
/BTN_1: J9.9, SW1.2
/BTN_2: J9.8, SW2.2
/DDS_CLK: J7.5, J8.10
/DDS_DAT: J7.4, J8.9
/DDS_FNC: J7.6, J9.10
/DDS_OUT: C5.1, J7.7, TP7.1 (1_1)
/ENC_CLK: J3.1, J9.5
/ENC_DT: J3.2, J9.6
/ENC_SW: J3.3, J9.7
/Reset_Vin: J9.3, R13.2, TP5.1 (1_1)
/Reset_Vout: J9.4, R14.2, TP6.1 (1_1)
/UART_RX: J2.2, J4.4, J8.4
/UART_TX: J2.1, J4.3, J8.3
/Vin: J6.1, R7.1, TP1.1 (1_1)
/Vin_pico: D5.2 (A), D6.1 (K), J9.1, R15.2, TP3.1 (1_1)
/Vout: J5.1, R6.2, R8.1, TP2.1 (1_1), U1.7
/Vout_pico: D7.2 (A), D8.1 (K), J9.2, R16.2, TP4.1 (1_1)
GND: C1.2, C2.1, C3.2, C4.1, C6.2, C7.2, C8.1, C9.2, C10.1, C11.2, C12.2, D6.2 (A), D8.2 (A), J1.2, J1.3, J2.3, J3.5, J4.5, J5.2, J6.2, J7.3, J8.2, J8.13, J9.13, Q1.1 (S), Q2.1 (S), R1.2, R3.2, R5.2, R11.2, R12.2, SW1.1, SW2.1, TP8.1 (1_1), TP9.1 (1_1), TP10.1 (1_1)
unnamed: C5.2, R1.1, R2.1
unnamed: D1.2 (A), R9.1, U2.2 (-)
unnamed: D1.1 (K), D3.2 (A), U2.1
unnamed: D2.2 (A), R10.1, U3.2 (-)
unnamed: D2.1 (K), D4.2 (A), U3.1
unnamed: C11.1, D3.1 (K), Q1.3 (D), U2.5 (+)
unnamed: C12.1, D4.1 (K), Q2.3 (D), U3.5 (+)
unnamed: Q1.2 (G), R11.1, R13.1
unnamed: Q2.2 (G), R12.1, R14.1
unnamed: C6.1, R2.2, U1.3 (+)
unnamed: R3.1, R4.1, U1.2 (-)
unnamed: R4.2, U1.1, U1.5 (+)
unnamed: R5.1, R6.1, U1.6 (-)
unnamed: R7.2, U2.3 (+)
unnamed: R9.2, R15.1, U2.6 (-), U2.7
unnamed: R8.2, U3.3 (+)
unnamed: R10.2, R16.1, U3.6 (-), U3.7

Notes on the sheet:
Filtro + Amplificador
ESP32-S3
Borneras
Detector de pico Vout
ESP32-S3 Touch-LCD-2 240x320 Pixels
Test points
Detector de pico Vin
